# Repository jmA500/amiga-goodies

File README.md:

# AMIGA Goodies

These are a few KiCad projects for PCBs that I created when dealing
with my Amigas. The PCBs might be useful for other people, so here they are.

All the PCBs are open hardware and free to use subject to the terms of
the GPLv2 licence. Refer to the file LICENSE for further details.

## FloppySwap

This is a Floppy-Swapper using a multiplexer 74HCT153 instead of an
elaborate mechanical switch. As it turns out this is more reliable and
even cheaper than the purely mechanical approach. As an extra benefit,
you can combine this with the Key-Tap to use your Keyboard to swap the
drives.

## CPU-Tap

A simple PCB that allows tapping the Processor signals on a .1" Pin
Header. Very useful for setting up a debugging rig.

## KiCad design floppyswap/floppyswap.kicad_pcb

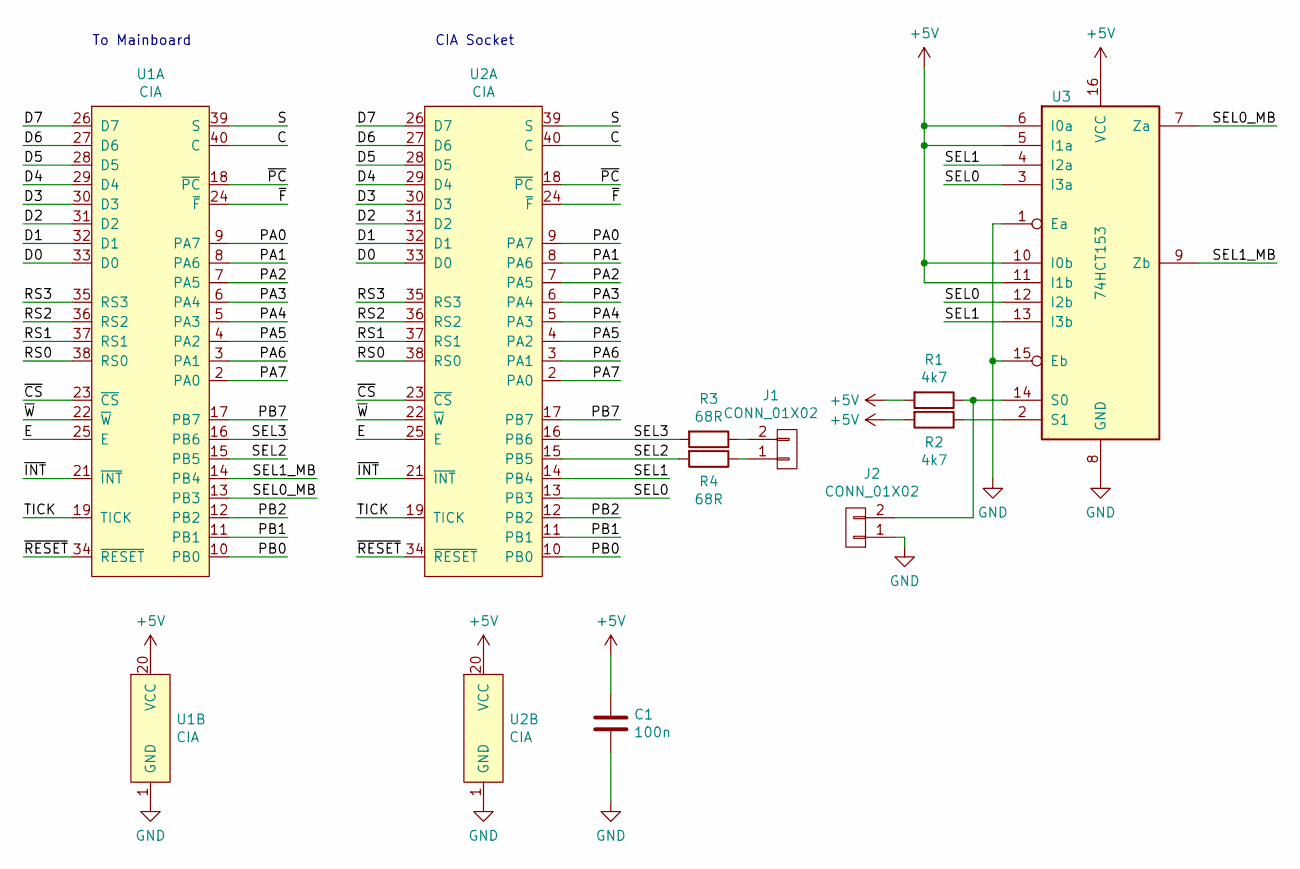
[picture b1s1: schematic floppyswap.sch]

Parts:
C1: 100n; C_0805
J1, J2: CONN_01X02; Pin_Header_Straight_1x02_Pitch2.54mm
R1, R2: 4k7; R_0805
R3, R4: 68R; R_0805
U1: CIA
U2: CIA; DIP-40_W15.24mm_Socket
U3: 74HCT153; DIP-16_W7.62mm

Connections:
+5V: C1.1, R1.2, R2.2, U1.20 (VCC), U2.20 (VCC), U3.5 (I1a), U3.6 (I0a), U3.10 (I0b), U3.11 (I1b), U3.16 (VCC)
/C: U1.40 (C), U2.40 (C)
/D0: U1.33 (D0), U2.33 (D0)
/D1: U1.32 (D1), U2.32 (D1)
/D2: U1.31 (D2), U2.31 (D2)
/D3: U1.30 (D3), U2.30 (D3)
/D4: U1.29 (D4), U2.29 (D4)
/D5: U1.28 (D5), U2.28 (D5)
/D6: U1.27 (D6), U2.27 (D6)
/D7: U1.26 (D7), U2.26 (D7)
/E: U1.25 (E), U2.25 (E)
/PA0: U1.9 (PA7), U2.9 (PA7)
/PA1: U1.8 (PA6), U2.8 (PA6)
/PA2: U1.7 (PA5), U2.7 (PA5)
/PA3: U1.6 (PA4), U2.6 (PA4)
/PA4: U1.5 (PA3), U2.5 (PA3)
/PA5: U1.4 (PA2), U2.4 (PA2)
/PA6: U1.3 (PA1), U2.3 (PA1)
/PA7: U1.2 (PA0), U2.2 (PA0)
/PB0: U1.10 (PB0), U2.10 (PB0)
/PB1: U1.11 (PB1), U2.11 (PB1)
/PB2: U1.12 (PB2), U2.12 (PB2)
/PB7: U1.17 (PB7), U2.17 (PB7)
/RS0: U1.38 (RS0), U2.38 (RS0)
/RS1: U1.37 (RS1), U2.37 (RS1)
/RS2: U1.36 (RS2), U2.36 (RS2)
/RS3: U1.35 (RS3), U2.35 (RS3)
/S: U1.39 (S), U2.39 (S)
/SEL0: U2.13 (PB3), U3.3 (I3a), U3.12 (I2b)
/SEL0_MB: U1.13 (PB3), U3.7 (Za)
/SEL1: U2.14 (PB4), U3.4 (I2a), U3.13 (I3b)
/SEL1_MB: U1.14 (PB4), U3.9 (Zb)
/SEL2: R4.2, U1.15 (PB5), U2.15 (PB5)
/SEL3: R3.2, U1.16 (PB6), U2.16 (PB6)
/TICK: U1.19 (TICK), U2.19 (TICK)
/~CS: U1.23 (~CS), U2.23 (~CS)
/~F: U1.24 (~F), U2.24 (~F)
/~INT: U1.21 (~INT), U2.21 (~INT)
/~PC: U1.18 (~PC), U2.18 (~PC)
/~RESET: U1.34 (~RESET), U2.34 (~RESET)
/~W: U1.22 (~W), U2.22 (~W)
GND: C1.2, J2.1, U1.1 (GND), U2.1 (GND), U3.1 (Ea), U3.8 (GND), U3.15 (Eb)
unnamed: J1.1, R4.1
unnamed: J1.2, R3.1
unnamed: J2.2, R1.1, U3.14 (S0)
unnamed: R2.1, U3.2 (S1)

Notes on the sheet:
To Mainboard
CIA Socket

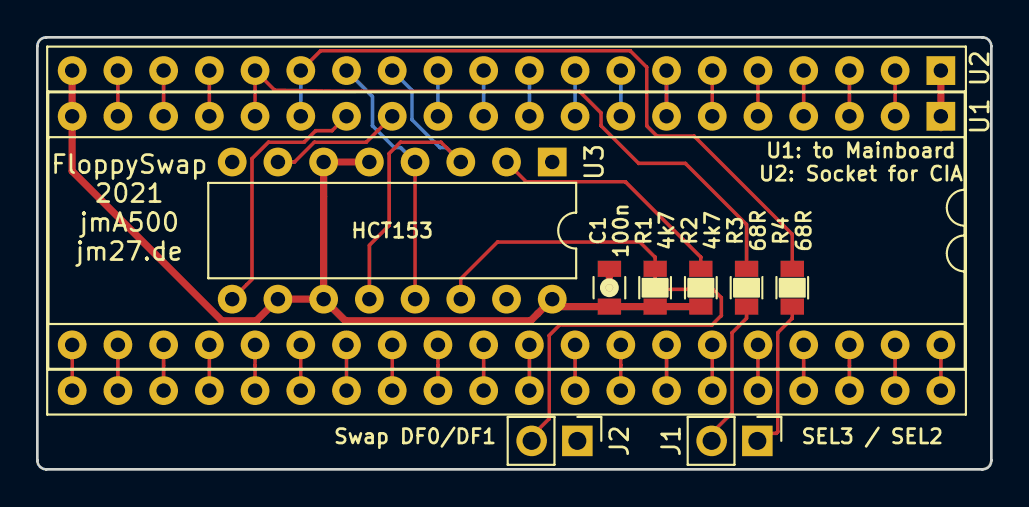
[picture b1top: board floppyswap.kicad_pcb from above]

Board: 2 copper layers, 53.0 x 24.0 mm, 10 parts (0 on the bottom side), 46 nets.

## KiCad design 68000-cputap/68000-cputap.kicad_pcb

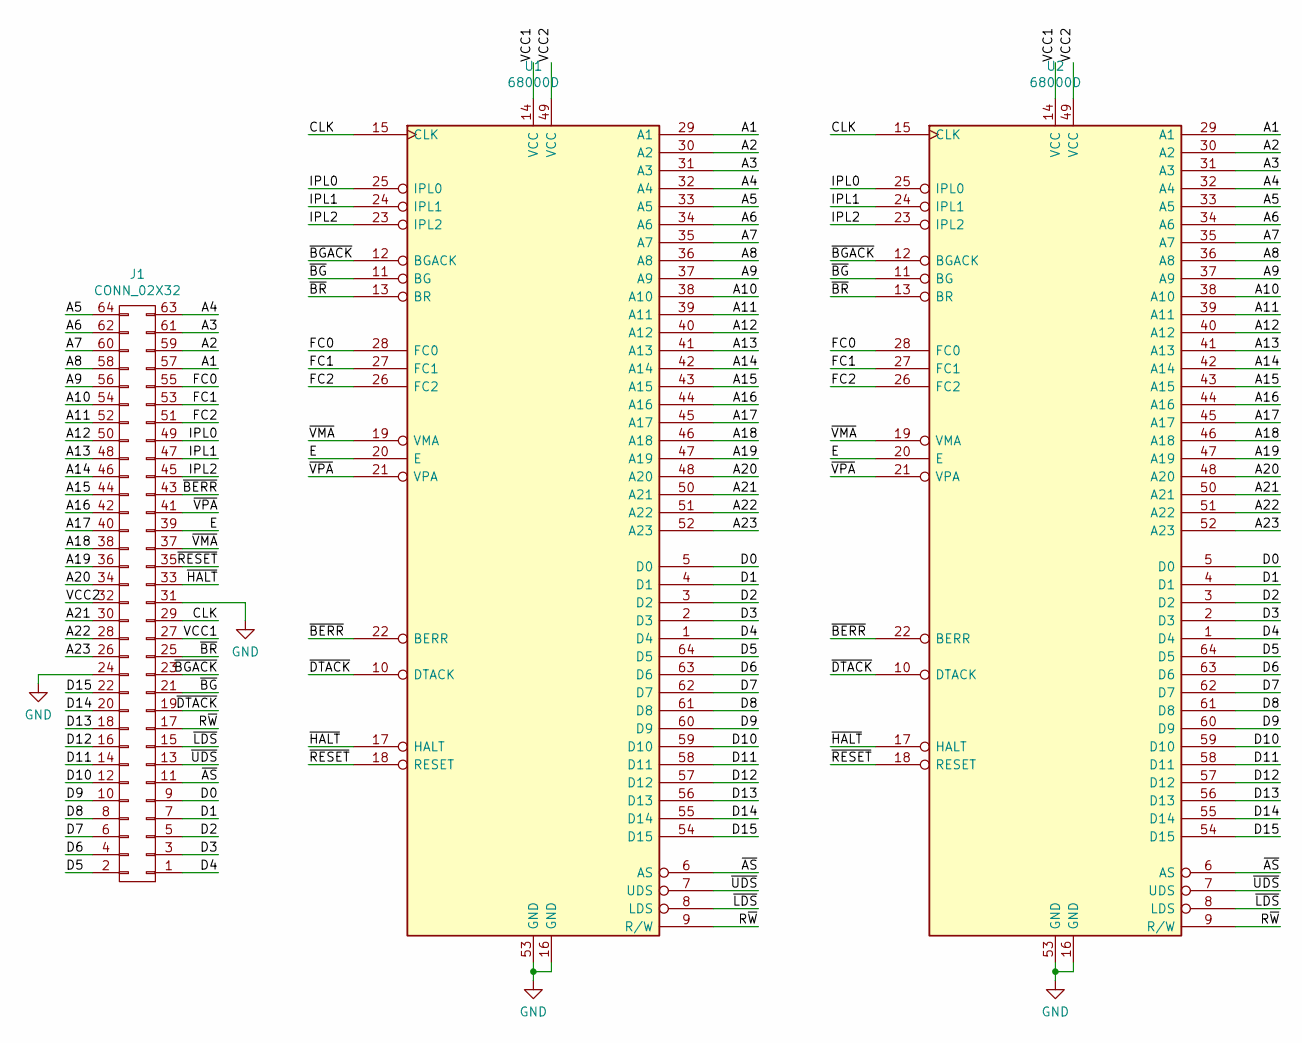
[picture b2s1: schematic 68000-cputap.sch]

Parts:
J1: CONN_02X32; Pin_Header_Straight_2x32_Pitch2.54mm
U1, U2: 68000D; DIP-64_W22.86mm

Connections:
/A1: J1.57, U1.29 (A1), U2.29 (A1)
/A2: J1.59, U1.30 (A2), U2.30 (A2)
/A3: J1.61, U1.31 (A3), U2.31 (A3)
/A4: J1.63, U1.32 (A4), U2.32 (A4)
/A5: J1.64, U1.33 (A5), U2.33 (A5)
/A6: J1.62, U1.34 (A6), U2.34 (A6)
/A7: J1.60, U1.35 (A7), U2.35 (A7)
/A8: J1.58, U1.36 (A8), U2.36 (A8)
/A9: J1.56, U1.37 (A9), U2.37 (A9)
/A10: J1.54, U1.38 (A10), U2.38 (A10)
/A11: J1.52, U1.39 (A11), U2.39 (A11)
/A12: J1.50, U1.40 (A12), U2.40 (A12)
/A13: J1.48, U1.41 (A13), U2.41 (A13)
/A14: J1.46, U1.42 (A14), U2.42 (A14)
/A15: J1.44, U1.43 (A15), U2.43 (A15)
/A16: J1.42, U1.44 (A16), U2.44 (A16)
/A17: J1.40, U1.45 (A17), U2.45 (A17)
/A18: J1.38, U1.46 (A18), U2.46 (A18)
/A19: J1.36, U1.47 (A19), U2.47 (A19)
/A20: J1.34, U1.48 (A20), U2.48 (A20)
/A21: J1.30, U1.50 (A21), U2.50 (A21)
/A22: J1.28, U1.51 (A22), U2.51 (A22)
/A23: J1.26, U1.52 (A23), U2.52 (A23)
/CLK: J1.29, U1.15 (CLK), U2.15 (CLK)
/D0: J1.9, U1.5 (D0), U2.5 (D0)
/D1: J1.7, U1.4 (D1), U2.4 (D1)
/D2: J1.5, U1.3 (D2), U2.3 (D2)
/D3: J1.3, U1.2 (D3), U2.2 (D3)
/D4: J1.1, U1.1 (D4), U2.1 (D4)
/D5: J1.2, U1.64 (D5), U2.64 (D5)
/D6: J1.4, U1.63 (D6), U2.63 (D6)
/D7: J1.6, U1.62 (D7), U2.62 (D7)
/D8: J1.8, U1.61 (D8), U2.61 (D8)
/D9: J1.10, U1.60 (D9), U2.60 (D9)
/D10: J1.12, U1.59 (D10), U2.59 (D10)
/D11: J1.14, U1.58 (D11), U2.58 (D11)
/D12: J1.16, U1.57 (D12), U2.57 (D12)
/D13: J1.18, U1.56 (D13), U2.56 (D13)
/D14: J1.20, U1.55 (D14), U2.55 (D14)
/D15: J1.22, U1.54 (D15), U2.54 (D15)
/E: J1.39, U1.20 (E), U2.20 (E)
/FC0: J1.55, U1.28 (FC0), U2.28 (FC0)
/FC1: J1.53, U1.27 (FC1), U2.27 (FC1)
/FC2: J1.51, U1.26 (FC2), U2.26 (FC2)
/IPL0: J1.49, U1.25 (IPL0), U2.25 (IPL0)
/IPL1: J1.47, U1.24 (IPL1), U2.24 (IPL1)
/IPL2: J1.45, U1.23 (IPL2), U2.23 (IPL2)
/R~W: J1.17, U1.9 (R/W), U2.9 (R/W)
/VCC1: J1.27, U1.14 (VCC), U2.14 (VCC)
/VCC2: J1.32, U1.49 (VCC), U2.49 (VCC)
/~AS: J1.11, U1.6 (AS), U2.6 (AS)
/~BERR: J1.43, U1.22 (BERR), U2.22 (BERR)
/~BG: J1.21, U1.11 (BG), U2.11 (BG)
/~BGACK: J1.23, U1.12 (BGACK), U2.12 (BGACK)
/~BR: J1.25, U1.13 (BR), U2.13 (BR)
/~DTACK: J1.19, U1.10 (DTACK), U2.10 (DTACK)
/~HALT: J1.33, U1.17 (HALT), U2.17 (HALT)
/~LDS: J1.15, U1.8 (LDS), U2.8 (LDS)
/~RESET: J1.35, U1.18 (RESET), U2.18 (RESET)
/~UDS: J1.13, U1.7 (UDS), U2.7 (UDS)
/~VMA: J1.37, U1.19 (VMA), U2.19 (VMA)
/~VPA: J1.41, U1.21 (VPA), U2.21 (VPA)
GND: J1.24, J1.31, U1.16 (GND), U1.53 (GND), U2.16 (GND), U2.53 (GND)

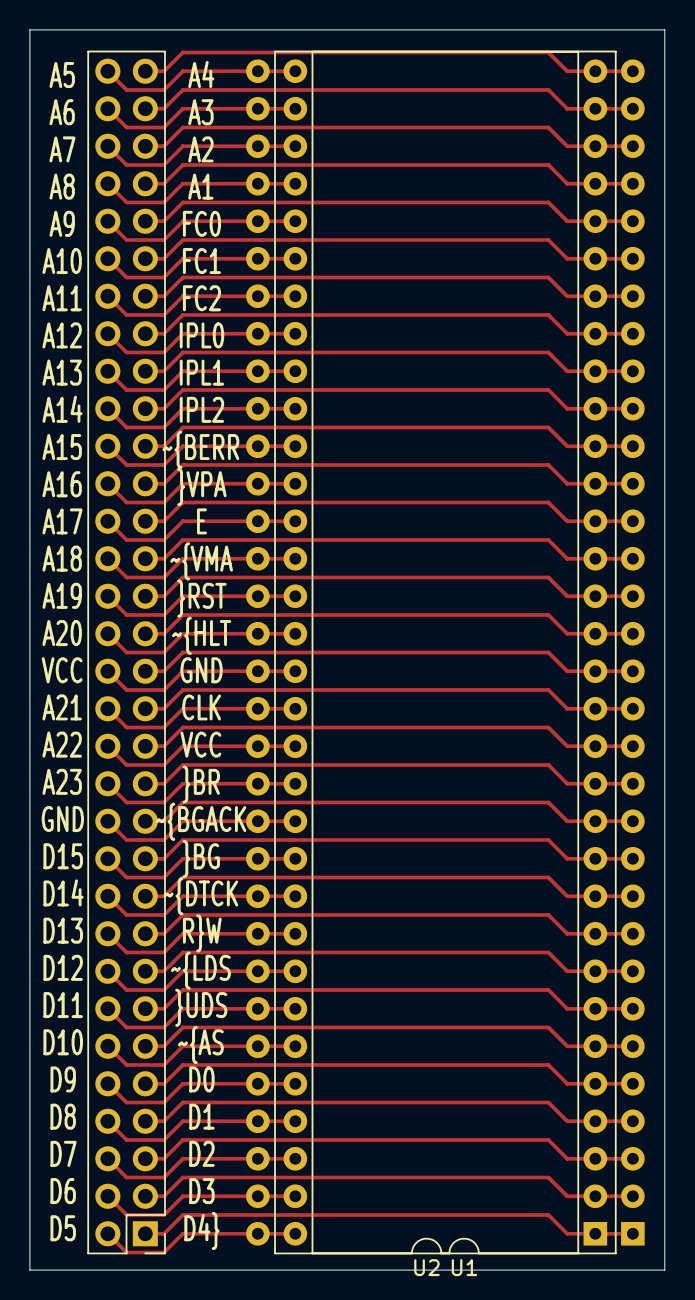
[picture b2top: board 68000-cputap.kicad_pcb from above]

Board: 2 copper layers, 43.0 x 84.0 mm, 3 parts (0 on the bottom side), 63 nets.

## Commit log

2021-03-13 Initial import Collecting a few small AMIGA-related projects
2021-03-13 Added README.md and LICENSE
2021-04-17 Added Rescue Libs to Repo
